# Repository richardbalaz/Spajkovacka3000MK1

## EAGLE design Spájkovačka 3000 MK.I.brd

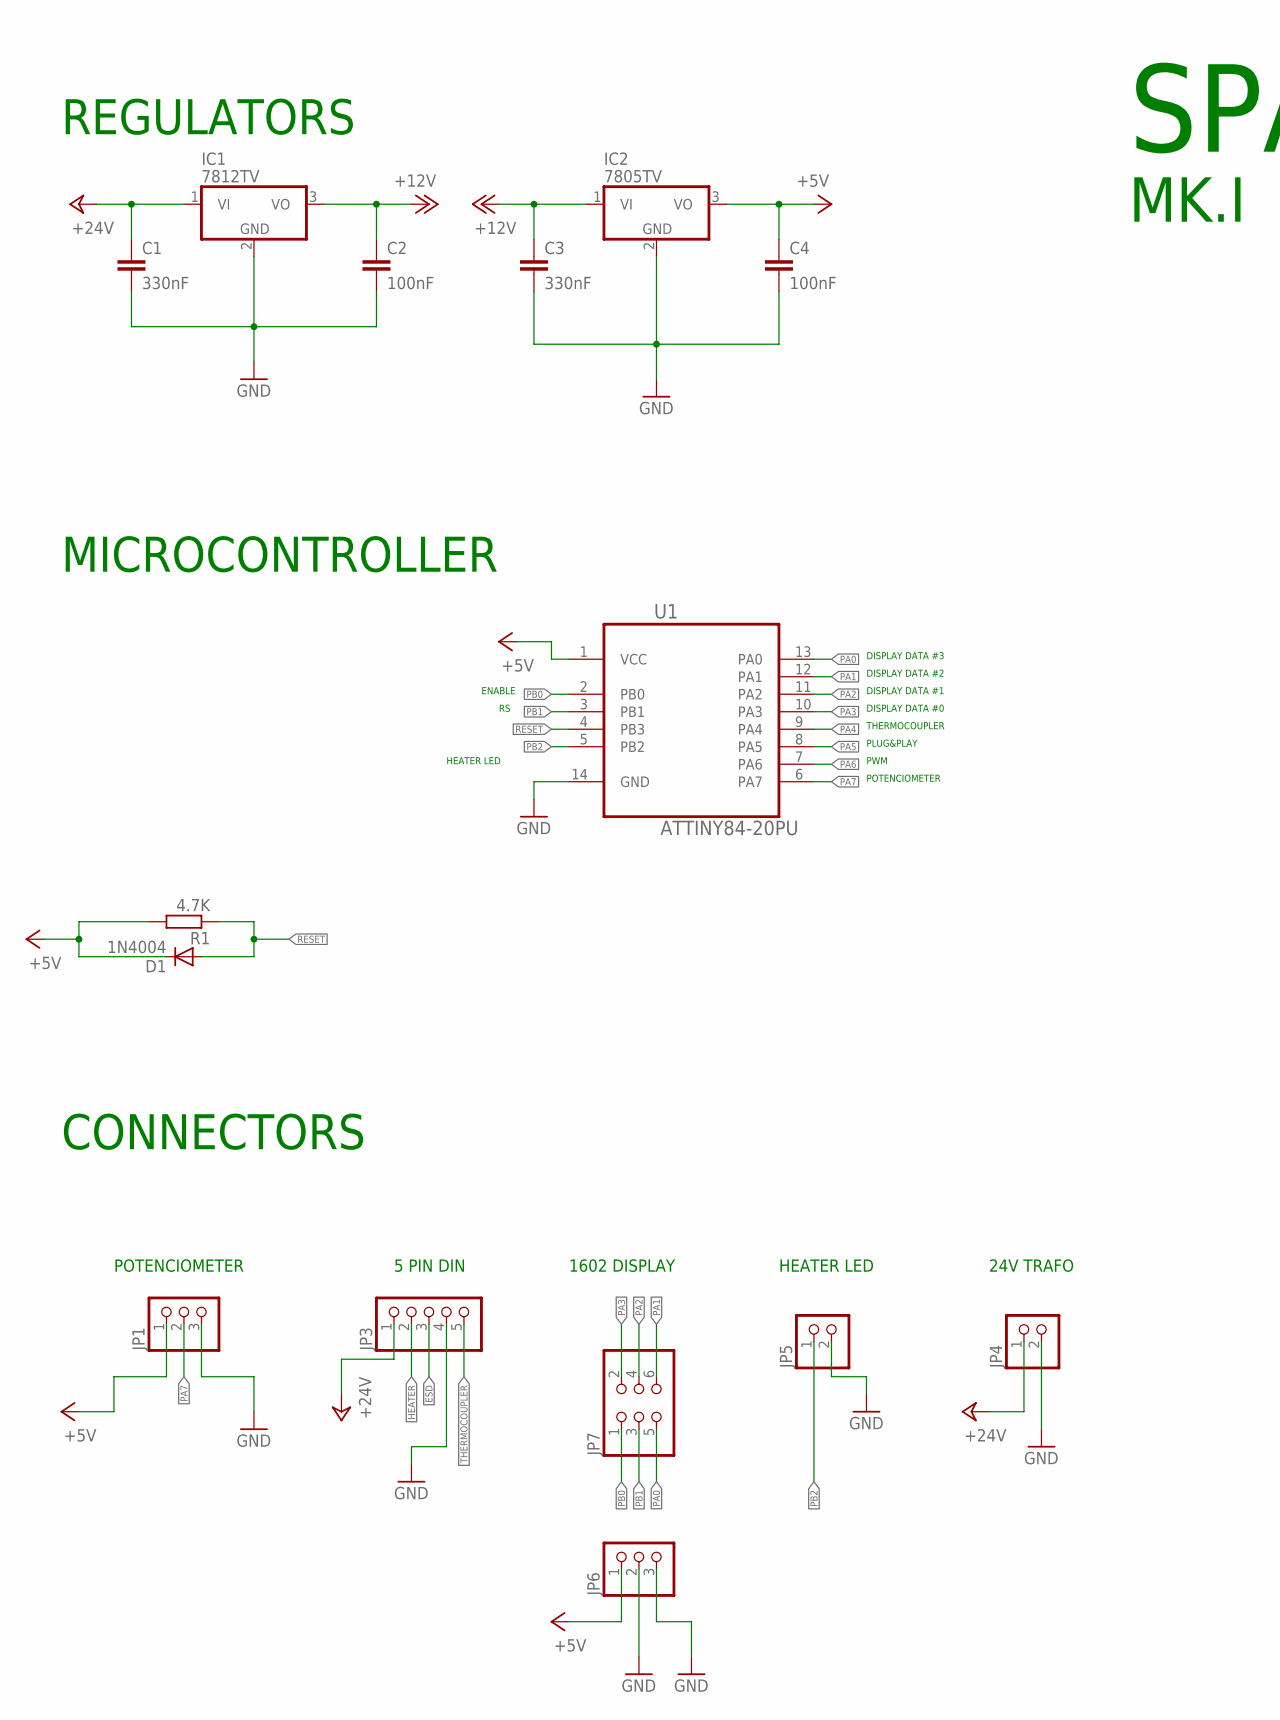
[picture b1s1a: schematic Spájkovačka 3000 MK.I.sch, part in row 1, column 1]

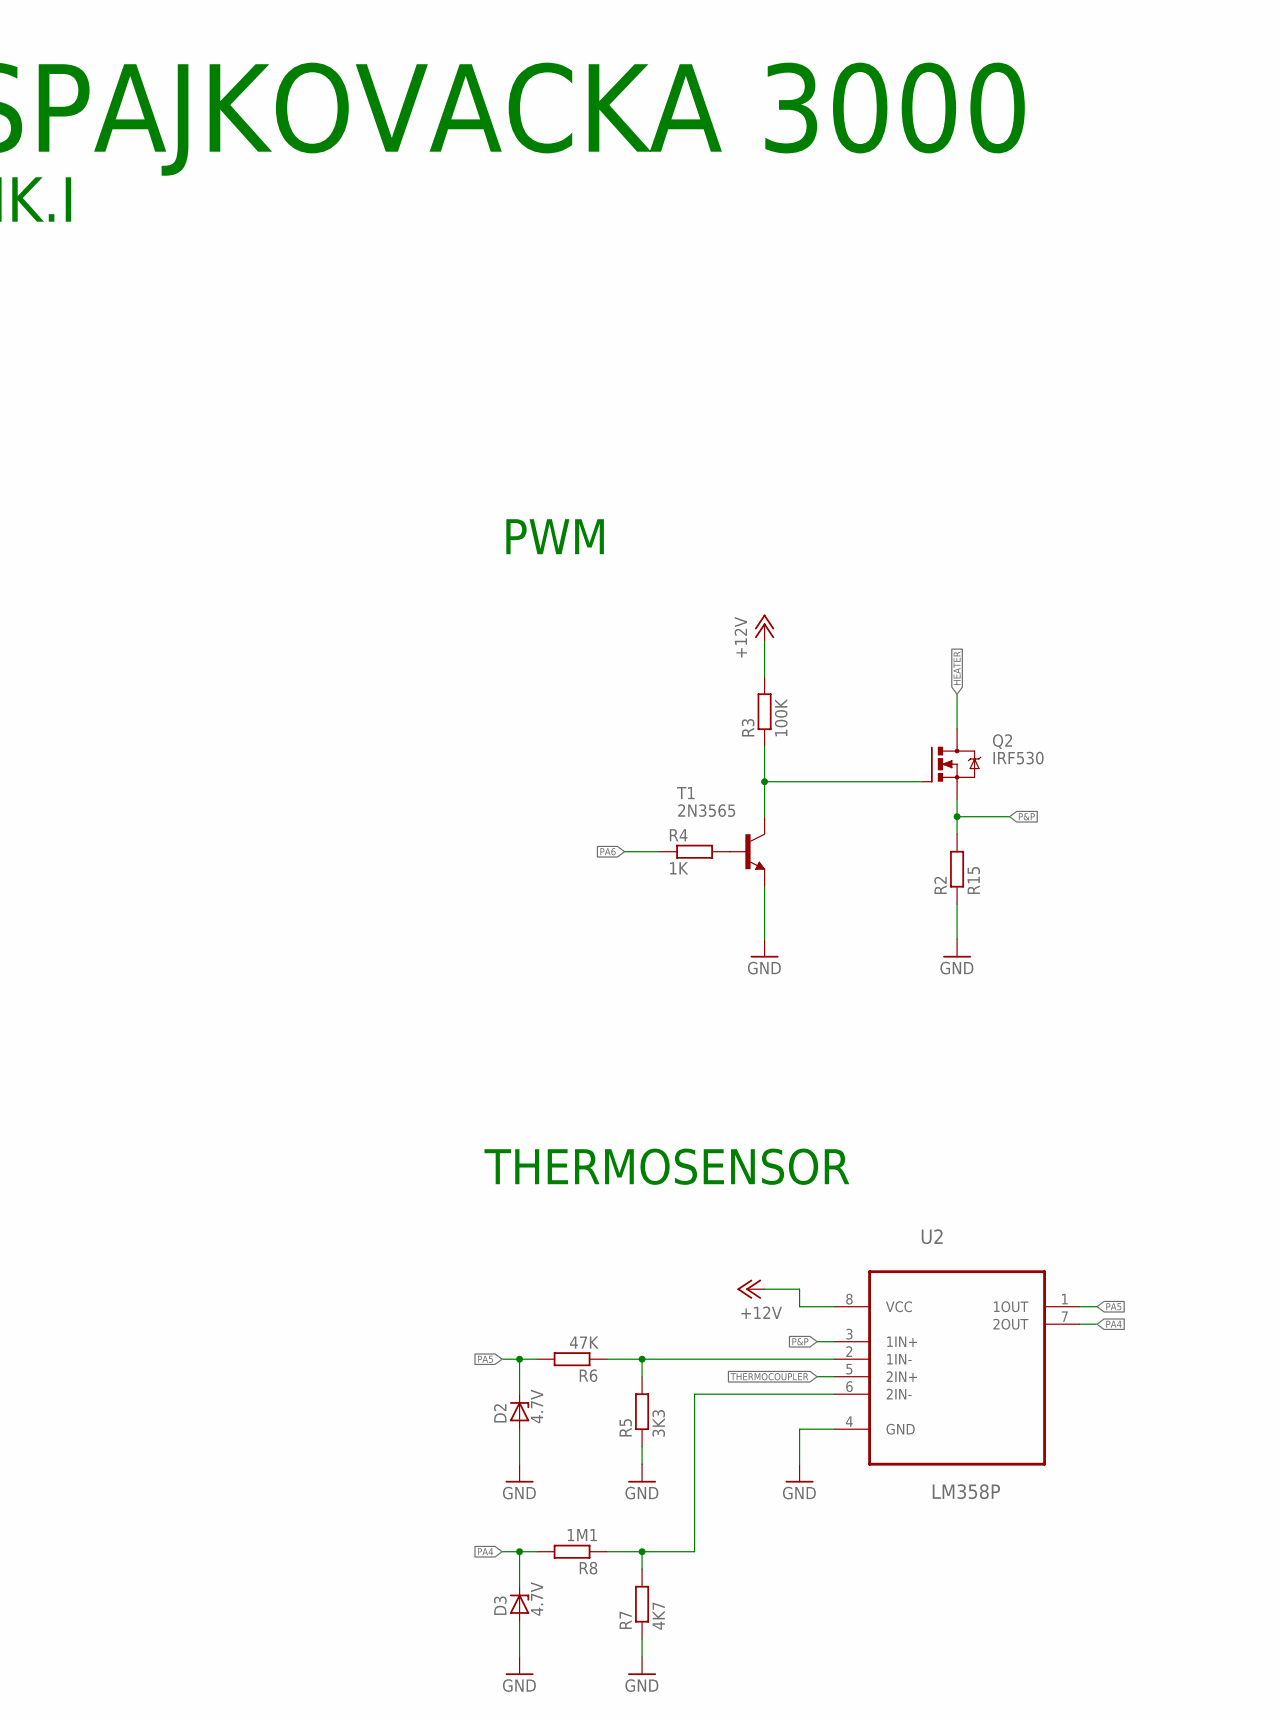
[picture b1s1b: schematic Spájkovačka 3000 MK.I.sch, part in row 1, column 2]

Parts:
C1, C3: 330nF; C025-024X044
C2, C4: 100nF; C025-024X044
D1: 1N4004; DO41-10
D2, D3: 4.7V; DO41Z10
IC1: 7812TV; TO220V
IC2: 7805TV; TO220V
JP1, JP6: PINHD-1X3; 1X03
JP3: PINHD-1X5; 1X05
JP4, JP5: PINHD-1X2; 1X02
JP7: PINHD-2X3; 2X03
Q2: IRF530; TO220BV
R1: 4.7K; 0207/10
R2: R15; 0922/22
R3: 100K; 0207/10
R4: 1K; 0207/10
R5: 3K3; 0207/10
R6: 47K; 0207/10
R7: 4K7; 0207/10
R8: 1M1; 0207/10
T1: 2N3565; TO92
U1: ATTINY84-20PU; DIP254P762X533-14
U2: LM358P; DIP254P762X508-8

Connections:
1IN-: R5.2, R6.1, U2.2 (1IN-)
+5V: C4.1, D1.C, IC2.3 (VO), JP1.1, JP6.1, R1.2, U1.1 (VCC)
+12V: C2.1, C3.1, IC1.3 (VO), IC2.1 (VI), R3.2, U2.8 (VCC)
+24V: C1.1, IC1.1 (VI), JP3.1, JP4.1
ESD: JP3.3
GND: C1.2, C2.2, C3.2, C4.2, D2.A, D3.A, IC1.2 (GND), IC2.2 (GND), JP1.3, JP3.4, JP4.2, JP5.2, JP6.2, JP6.3, R2.1, R5.1, R7.1, T1.3 (E), U1.14 (GND), U2.4 (GND)
HEATER: JP3.2, Q2.D
unnamed: R7.2, R8.1, U2.6 (2IN-)
unnamed: Q2.G, R3.1, T1.1 (C)
unnamed: R4.2, T1.2 (B)
P&P: Q2.S, R2.2, U2.3 (1IN+)
PA0: JP7.5, U1.13 (PA0)
PA1: JP7.6, U1.12 (PA1)
PA2: JP7.4, U1.11 (PA2)
PA3: JP7.2, U1.10 (PA3)
PA4: D3.C, R8.2, U1.9 (PA4), U2.7 (2OUT)
PA5: D2.C, R6.2, U1.8 (PA5), U2.1 (1OUT)
PA6: R4.1, U1.7 (PA6)
PA7: JP1.2, U1.6 (PA7)
PB0: JP7.1, U1.2 (PB0)
PB1: JP7.3, U1.3 (PB1)
PB2: JP5.1, U1.5 (PB2)
RESET: D1.A, R1.1, U1.4 (PB3)
THERMOCOUPLER: JP3.5, U2.5 (2IN+)

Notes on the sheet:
CONNECTORS
REGULATORS
MICROCONTROLLER
POTENCIOMETER
5 PIN DIN
PWM
PLUG&PLAY
THERMOCOUPLER
1602 DISPLAY
HEATER LED
DISPLAY DATA #0
DISPLAY DATA #1
DISPLAY DATA #2
DISPLAY DATA #3
ENABLE
THERMOSENSOR
SPAJKOVACKA 3000
24V TRAFO
MK.I

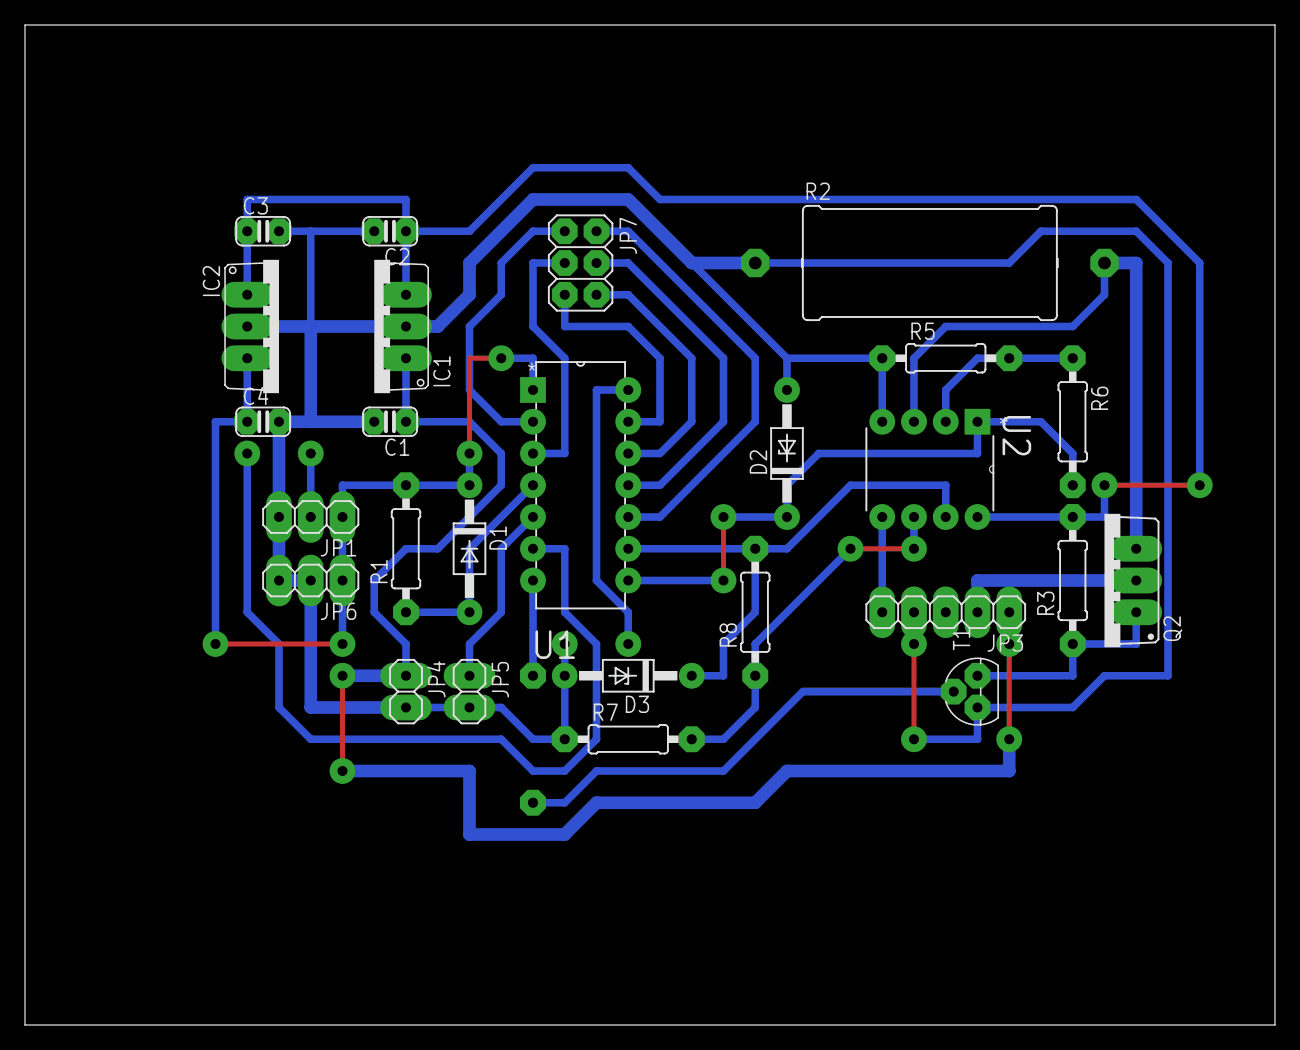
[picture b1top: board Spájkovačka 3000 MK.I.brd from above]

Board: 2 copper layers, 100.0 x 80.0 mm, 27 parts (1 on the bottom side), 23 nets.
